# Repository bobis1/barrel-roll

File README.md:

# barrel-roll

_Slightly dissassembled view of barrel roll._

Currently there are some issues with this project
## TODO
- Fix the pcb to have the correct footprint

## What is this
Barrel roll is a 150g combat robot that has a 2.706693 inch long bar spinner. There are two options for the microcontroller of the robot. Right now I have a pcb designed with a RP2040 in mind. I also have a version of the schematic/firmware with an esp32 as the microcontroller.

## Why I created this
I created barrel roll because the way I got into robotics/programming/stem in general is through watching various battlebots-like shows and videos on the internet. So for a long time, I wanted to create my own battle bot. Once I saw the Fallout event by Hack Club I decided that it would be an amazing opportunity to create something similar to what got me into this in the first place. My goal with barrel roll is to create a bar spinner battle bot that could compete in the 150g weight class.(not necessarily well)

## PCB

Above are the images of the PCB version of the electrical components of the robot(To be honest right now it feels more like a glorified pinout board)

Above is a picture of the pcb using DIP sodering. The schematic is the same as the original SMD sodered PCB.

The above is a picture of the schematic for anyone using the DOIT esp32 devkit v1. I made this one because it could cut down on the cost of the project as a whole.

## Assembly
Onshape link: https://cad.onshape.com/documents/4d0cf8c11fd66439fc3e30b0/w/a8064dfad10d7d33689fe150/e/62081654516d84e6ca0ee160

A note about the assembly: I could not find 3d models of the bearings I wanted to use so I made a model with the same dimensions as the bearings. /n

As a note I intend on using the PCB SMD BOM.

### PCBs/Electronics
For this project I made several usable versions of the electronics. I did this to make sure that when it comes time for me to actually build this I can still build it even if I don't have some of the equipment that I need. The main distinction between all of the options are the different ways to soder on the microcontroller. For the no pcb method you could just use an esp32 instead of a xiao rp2040.

#### PCB SMD
IF you are using a PCB to create Barrel Roll then you need to get the Gerbers.zip from barrel-roll folder in the repo. After this you need to go to your preferred PCB manufacteror of your choice to have it manufactured.  [Gerbers.zip](barrel-roll-pcb/Gerbers.zip)
You could use [this](https://fabacademy.org/2024/labs/charlotte/students/richard-shan/lessons/week4/rp2040/) as a reference for SMD sodering the xiao RP2040.

#### PCB DIP
If you are using the DIP version of the pcb then you need to follow many of the same steps as using the SMD pcb method. However, since you are using DIP for the RP2040, sodering the PCB should be significantly simpler. [Gerbers.zip](barrel-roll-DIPPCB/Gerbers.zip)

#### No PCB
If you are not using a PCB your costs will be a little bit lower since you don't need to by the PCB. To find the wiring diagram you can look in the barrel-roll-nopcb folder of the repo. This is a kicad project that contains a wiring diagram if you have a DOIT ESP32 devkit 1(The esp32 from the electronics kits that commonly come from hackclub events).

#### Assembling the weapon system shell
In order to assemble the weapon system properly you want to make sure that you place the parts on the axle in the correct order. Axle stopper, Weapon with bearing, Axle stopper. Then you need to place the axle onto the two pieces on the Side shell.

Here is a picture of the front assembly that you should try to replicate.

#### 3D printing
To assemble the barrel-roll you first need to print out the parts specified in the onshape document. All the parts in the FINAL folder must be printed There will be a note with the quantity and the infill amount. The fillament for all of these will be up to you. I will personally be using TPU. If you do not want to go into the Onshape, All of the final .step files will be in [models/FinalParts](CAD/V5).\

 You need to print:
* 1 BodyFinalPart1.step [Link](CAD/V5/BodyFinalPart1.step)
* 1 BodyFinalPart2.step [Link](CAD/V5/BodyFinalPart2.step)
* 2 n20motorToWheel.step [Link](CAD/V5/n20motorToWheel.step)
* 1 ShaftCap [Link](CAD/V5/ShaftCapFinal.step)
* 1 WeaponDirectDrive.step [Link](CAD/V5/WeaponDirectDrive.step)
* Weapon Cap [Link](CAD/V5/WeaponMotorCap.step)

#### Assembling the shell
##### For context:

[.Step File](CAD/V5/BodyFinalPart1.step)
The above is the main shell

[.Step File](CAD/V5/BodyFinalPart2.step)

The above is the side shell
For the rest of it you should look at the onshape document.

To assemble the Main shell with the Side Shells you can use the bowtie connector along side the fastening rod to attach each part of the SIDE_SHELL without the use of metal connectors. To do this, follow the instructions below.

- 1. you first need to slide the shell into place directly into the bowtie connector. The next thing you want to do is slot in the pin connectors into the respective hole.
 [video](ReadmeAssets/SideAssembly1.mov). (Yes I knbow the video is outdated I made the video before making a bunch of design changes relating to the side shell.)

- 2. After this you want to slide the shaft onto the side piece. The next thing that you want to do is attach a shaft cap directly on the inside of the side shell. [video](ReadmeAssets/ShaftAssembly1.mov). 

- 3. You need to slide the weapon onto the shaft. Next you need to slide the other shaft cap onto the shaft.
[video](ReadmeAssets/ShaftAssembly2.mov). After you do this you need to attach the belt to the timing wheel of the weapon.

- 4. The next thing that you need to do is you need to repeat step 1 for the other side of the case. With this you are finished with the shell assembly.

#### Assembling the weapon motor system
Assemblint the weapon system involves, using the weapon motor screws to secure the motor to the side of the shell with the "shield" like so . Next to finish securing the weapon onto the motor, simply slide the weapon onto the motor shaft then place the cap onto the motor shaft like so .
With this you are almost done with the weapon motor system. n/

The next thing that you need to do is slide the shaft into the bearings. Before doing this you need to cut the (90mm) shaft into a 60mm shaft.(The reason for this is to cut down on the weight and to to make the shaft super long.) An alternative to this would be to print out a similarly sized rod out of ABS or petg [Here](CAD/V5/shaft.step)

#### Electronics
For the electronics you want to reference the [Schematic](ReadmeAssets/barrel-roll.pdf) and the . First you want to wire the drive motors to AOUT and BOUT pin holes respectively. Do this for both of the drive motors. The next thing that you want to do is attach the motor driver to the respective pins. Next you have to attach the ESC motor controller for the brushless motor. Next you have to soder the jumper wires to their respective ports based on the schematic of the pcb. The schematic should have all the pins that you need to soder to.

## Usage
To use barrel roll you need to connect the radio recever to the radio sender.
After this you should be able to control the robot using your controller.

## BOM
There are three BOMs one for SMD, DIP and one if you are simply using a esp32.
The "master" BOM can be found here [BOM](ReadmeAssets/BOM.csv)(This will be the most convienient to use and will be the most updated in the coming months.)
### BOM for PCB
 [Here is the .csv for the BOM](ReadmeAssets/BarrelRollerBOM.csv)
### BOM if you are not using a PCB
 [Here is the .csv for the BOM](ReadmeAssets/BarrelRollerBOMnopcb.csv)
### BOM PCB-DIP
 [Here is the .csv for the BOM](ReadmeAssets/BarrelRollerBOMDIP.csv)

## Poster

[Poster](Poster/Barrel%20Roller.pdf)

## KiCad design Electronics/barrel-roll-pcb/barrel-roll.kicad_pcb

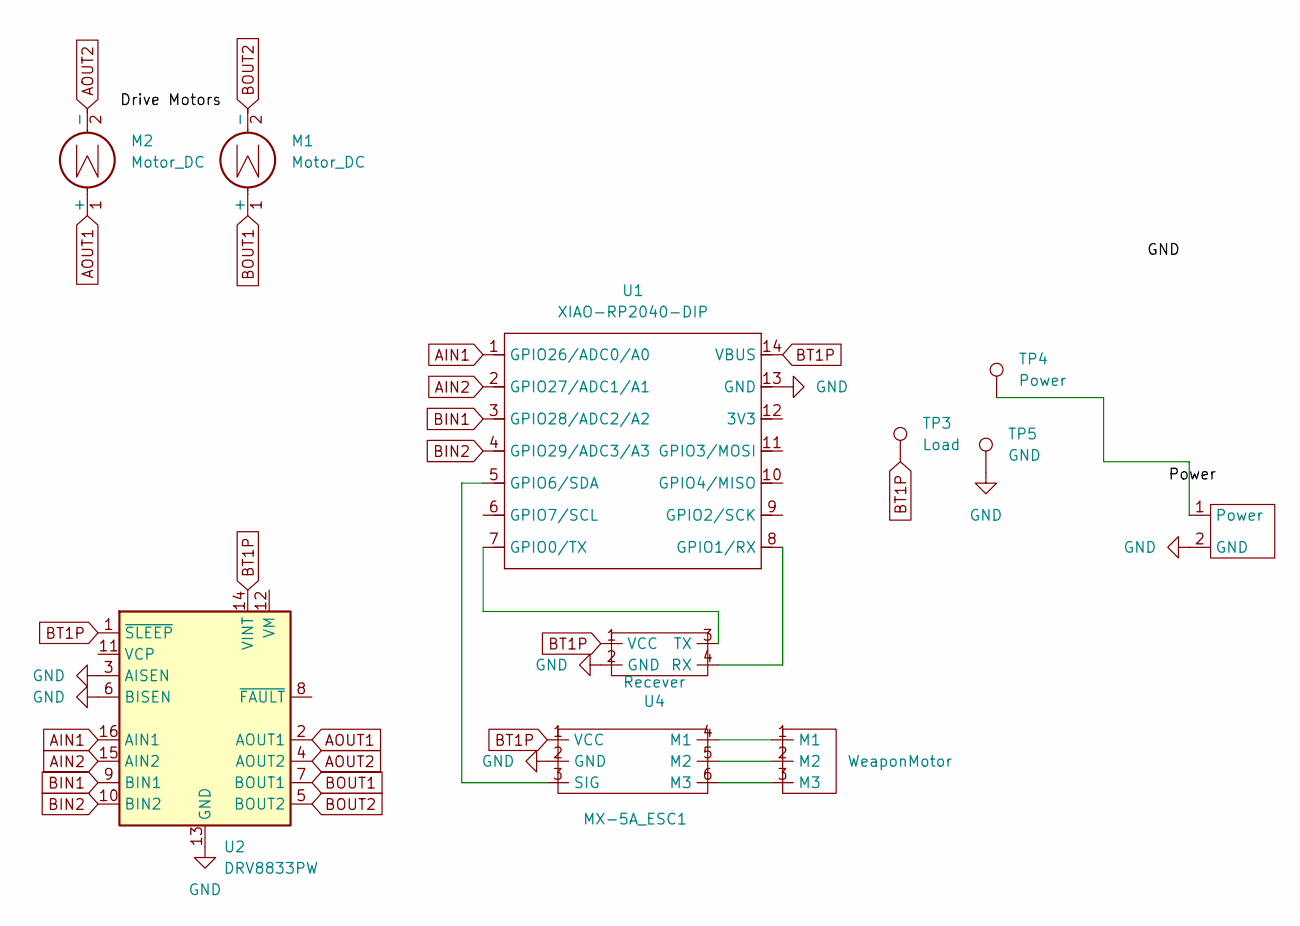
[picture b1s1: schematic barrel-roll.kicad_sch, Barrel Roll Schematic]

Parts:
M1, M2: Motor_DC; PinHeader_1x02_P2.54mm_Vertical
MX-5A_ESC1: PinHeader_1x06_P2.54mm_Vertical
TP3: Load; SolderWire-0.1sqmm_1x01_D0.4mm_OD1mm
TP4: Power; SolderWire-0.1sqmm_1x01_D0.4mm_OD1mm
TP5: GND; SolderWire-0.1sqmm_1x01_D0.4mm_OD1mm
U1: XIAO-RP2040-DIP; XIAO-RP2040-SMD
U2: DRV8833PW; DIP-16_W7.62mm
U3: WeaponMotor; PinHeader_1x03_P2.54mm_Vertical
U4: Recever; PinHeader_1x04_P2.54mm_Vertical
XT1: AMASS_XT30UPB-F_1x02_P5.0mm_Vertical

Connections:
AIN1: U1.1 (GPIO26/ADC0/A0), U2.16 (AIN1)
AIN2: U1.2 (GPIO27/ADC1/A1), U2.15 (AIN2)
AOUT1: M2.1 (+), U2.2 (AOUT1)
AOUT2: M2.2 (-), U2.4 (AOUT2)
BIN1: U1.3 (GPIO28/ADC2/A2), U2.9 (BIN1)
BIN2: U1.4 (GPIO29/ADC3/A3), U2.10 (BIN2)
BOUT1: M1.1 (+), U2.7 (BOUT1)
BOUT2: M1.2 (-), U2.5 (BOUT2)
BT1P: MX-5A_ESC1.1 (VCC), TP3.1 (1_1), U1.14 (VBUS), U2.1 (~SLEEP), U2.14 (VINT), U4.1 (VCC)
GND: MX-5A_ESC1.2 (GND), TP5.1 (1_1), U1.13 (GND), U2.3 (AISEN), U2.6 (BISEN), U2.13 (GND), U4.2 (GND), XT1.2 (GND)
unnamed: MX-5A_ESC1.4 (M1), U3.1 (M1)
unnamed: MX-5A_ESC1.5 (M2), U3.2 (M2)
unnamed: MX-5A_ESC1.6 (M3), U3.3 (M3)
unnamed: MX-5A_ESC1.3 (SIG), U1.5 (GPIO6/SDA)
unnamed: U1.7 (GPIO0/TX), U4.3 (TX)
unnamed: U1.8 (GPIO1/RX), U4.4 (RX)
unnamed: TP4.1 (1_1), XT1.1 (Power)

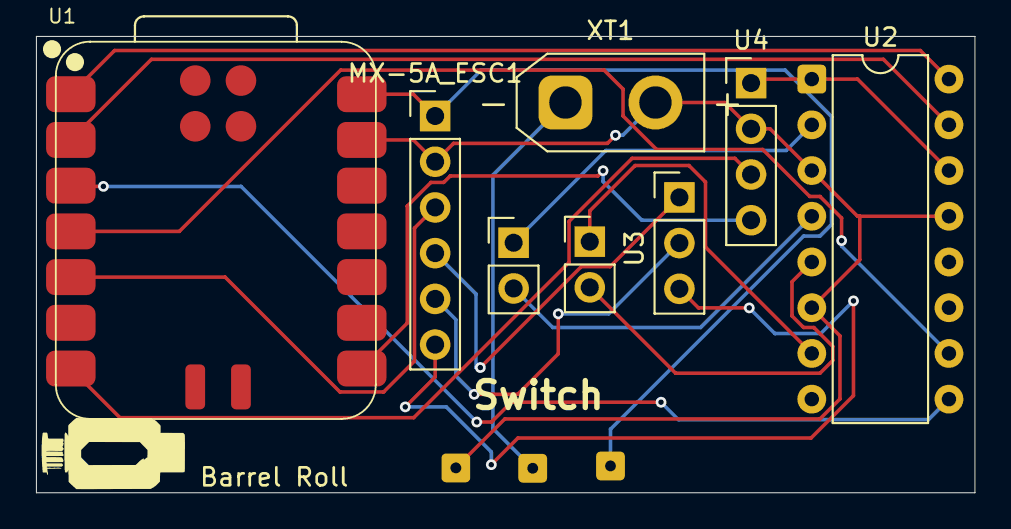
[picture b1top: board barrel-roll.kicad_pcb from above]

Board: 2 copper layers, 52.1 x 25.3 mm, 11 parts (0 on the bottom side), 17 nets.

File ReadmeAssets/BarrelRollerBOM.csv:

Reference,Qty,Part,Footprint,Supplier ,Unit Price,Total Price,Weight,SubTotal:,$79.00
U1,1,XIAO-RP2040-DIP,Seeed Studio XIAO Series Library:XIAO-RP2040-DIP,https://www.seeedstudio.com/XIAO-RP2040-v1-0-p-5026.html,$3.99,$3.99,,Shipping:,$35.37
U2,1,DRV8833PW,Package_DIP:DIP-16_W7.62mm,https://www.pololu.com/product/2130/resources,$10.95,$10.95,,Tax:,$4.05
U3,1,WeaponMotor,Connector_PinHeader_2.54mm:PinHeader_1x03_P2.54mm_Vertical,https://itgresa.com/product/d2822-8-brushless-motor-outrunner/,$15.49,$15.49,,Total:,$118.42
U4,1,Recever,Connector_PinHeader_2.54mm:PinHeader_1x04_P2.54mm_Vertical,https://radiomasterrc.com/collections/elrs-receivers/product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,$11.99,$11.99,,Hours Required:,23.68
n/a,2,Bearings,n/a,https://www.aliexpress.us/item/2271799817221155.html?spm=a2g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,$0.65,$1.30,,,
n/a,1,Shaft,n/a,https://www.aliexpress.us/item/3256805290944526.html?spm=a2g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,$0.99,$0.99,,,
n/a,1,Heatset Inserts,n/a,https://www.aliexpress.us/item/3256807895940353.html?spm=a2g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,$0.99,$0.99,,,
n/a,1,LIPO battery,Connector_Wire:SolderWire-2sqmm_1x01_D2mm_OD3.9mm,https://www.racedayquads.com/products/rdq-series-11-4v-3s-72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,$18.49,$18.49,,,
XT1,1,XT60,Connector_AMASS:AMASS_XT30UPB-F_1x02_P5.0mm_Vertical,https://www.pololu.com/product/2175,$2.95,$2.95,,,
n/a,2,N20 Motor,dc_motor,https://www.aliexpress.us/item/2255800106854951.html?spm=a2g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,0.99,$1.98,,,
n/a,1,PCB,n/a,https://cart.jlcpcb.com/quote?spm=jlcpcb.Public.2006,$2.10,$2.10,,,
n/a,1,Weapon Motor Screws,n/a,https://www.homedepot.com/p/Everbilt-M3-0-5-x-12mm-Zinc-Flat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,$1.95,$1.95,,,
n/a,4,Drive Motor Screw,n/a,https://www.metricscrews.us/index.php?main_page=product_info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,$0.65,$2.60,,,
n/a,1,Timing Belt,n/a,https://www.aliexpress.us/item/3256806230097622.html?spm=a2g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,$3.23,$3.23,,,

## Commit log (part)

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2026-04-12 Got the pcb done.
2026-04-17 Worked on the firmware of the bot
2026-04-18 Added updated models
2026-04-19 Worked on renders and poster
2026-04-21 Added esp32 support, and worked on the battery conenctor.
2026-04-22 Worked on getting the weights correct.
2026-04-22 Updated the pcb and the models.
2026-04-23 Cleaned up the models folder abit
2026-04-23 At this point I am really just trying to polish everything up good progress on that though.
2026-04-24 Added pcb design elements.
2026-04-25 Worked on the readme and adding some silkscreen art onto the pcb
2026-04-26 Tried to create a rf recever
2026-04-29 Organized the repo
2026-04-30 Updated poster, readme, and render
2026-05-02 Updated PCB to have a DIP version and improved readme.
2026-05-02 Added BOMs
2026-05-02 Updated readme and organized the repo slightly
2026-05-02 forgor to add something to the readme.
2026-05-10 Worked on redoing the render for barrel roll
2026-05-11 Worked on the renders
2026-05-12 Worked on blender
2026-05-13 WOrked on the assembly instructions
    horrible progress
2026-05-17 Updated renders
2026-05-18 Polished the repo and got the finalized .step files for 3d pritners
2026-05-20 Worked on the readme of the barrel roll
2026-05-20 Wrapped up readme
2026-05-20 Updated onshape link
2026-06-07 Updated Gerbers
